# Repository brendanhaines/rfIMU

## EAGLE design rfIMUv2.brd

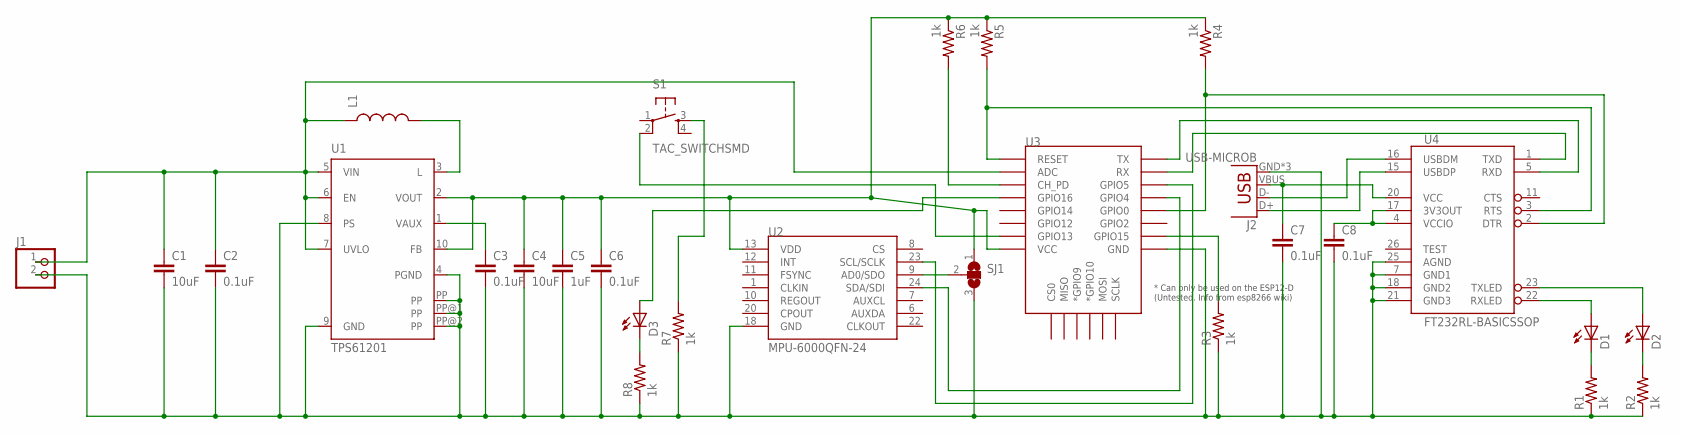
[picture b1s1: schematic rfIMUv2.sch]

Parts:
C1, C4: 10uF; C0603
C2, C3, C6, C7, C8: 0.1uF; C0603
C5: 1uF; C0603
D1, D2: LEDCHIPLED_0603; CHIPLED_0603
D3: LEDCHIP-LED0603; CHIP-LED0603
J1: PINHD-1X2; 1X02
J2: USB-MICROB
L1: INDUCTOR0805; 0805
R1, R2, R3, R4, R5, R6, R7, R8: 1k; R0603
S1: TAC_SWITCHSMD; TACTILE-SWITCH-SMD
SJ1: SJ2W; SJ_2
U1: TPS61201; S-PDSO-N10
U2: MPU-6000QFN-24; QFN-24-TESTING
U3: ESP12ESMD; ESP12E-SMD
U4: FT232RL-BASICSSOP; SSOP28DB

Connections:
3V3: C4.1, C5.1, C6.1, R4.1, R5.1, R6.1, SJ1.1, U1.2 (VOUT), U1.10 (FB), U2.13 (VDD), U3.VCC
D2: D2.C, R2.2
DRX: U3.RXD0 (RX), U4.1 (TXD)
DTR: R4.2, U3.GPIO0, U4.2 (DTR)
DTX: U3.TXD0 (TX), U4.5 (RXD)
GND: C1.2, C2.2, C3.2, C4.2, C5.2, C6.2, C7.2, C8.2, J1.2, J2.GND, J2.MT1 (GND), J2.MT2 (GND), R1.1, R2.1, R3.1, R7.1, R8.1, SJ1.3, U1.4 (PGND), U1.8 (PS), U1.9 (GND), U1.PP, U1.PP@1 (PP), U1.PP@2 (PP), U2.18 (GND), U3.GND, U4.7 (GND1), U4.18 (GND2), U4.21 (GND3), U4.25 (AGND)
unnamed: R3.2, U3.GPIO15
unnamed: R6.2, U3.CH_PD
unnamed: D2.A, U4.23 (TXLED)
unnamed: D1.A, U4.22 (RXLED)
unnamed: D1.C, R1.2
unnamed: C3.1, U1.1 (VAUX)
unnamed: SJ1.2, U2.9 (AD0/SDO)
unnamed: C8.1, U4.4 (VCCIO), U4.17 (3V3OUT)
unnamed: L1.2, U1.3 (L)
unnamed: S1.2, U3.GPIO13
unnamed: R7.2, S1.3
unnamed: D3.A, U3.GPIO16
unnamed: D3.C, R8.2
RESET: R5.2, U3.RESET, U4.3 (RTS)
SCL: U2.23 (SCL/SCLK), U3.GPIO5
SDA: U2.24 (SDA/SDI), U3.GPIO4
USBD+: J2.D+, U4.15 (USBDP)
USBD-: J2.D-, U4.16 (USBDM)
VIN: C1.1, C2.1, J1.1, L1.1, U1.5 (VIN), U1.6 (EN), U1.7 (UVLO), U3.ADC
VUSB: C7.1, J2.VBUS, U4.20 (VCC)

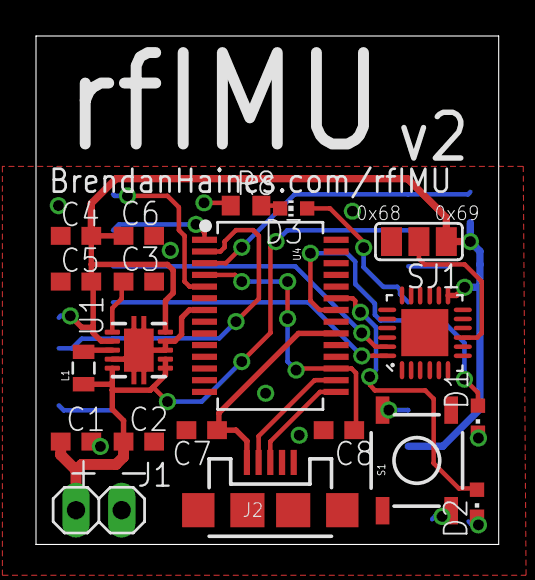
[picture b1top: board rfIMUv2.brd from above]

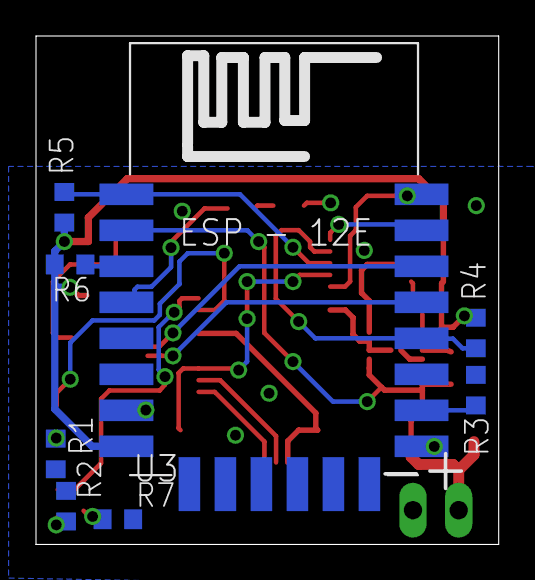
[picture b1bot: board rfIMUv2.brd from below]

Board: 2 copper layers, 25.7 x 28.2 mm, 28 parts (8 on the bottom side), 26 nets.

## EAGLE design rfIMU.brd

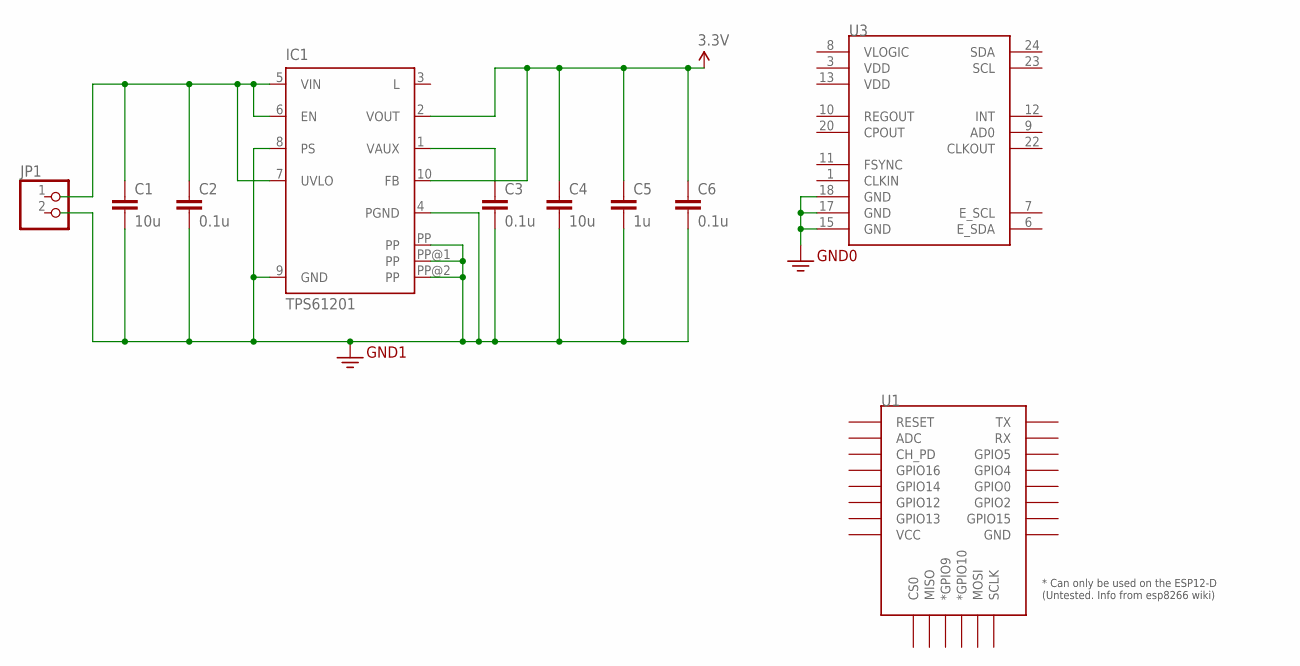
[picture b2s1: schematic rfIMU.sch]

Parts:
C1, C4: 10u; 0603
C2, C3, C6: 0.1u; 0603
C5: 1u; 0603
IC1: TPS61201; S-PDSO-N10
JP1: PINHD-1X2; 1X02
U1: ESP12ESMD; ESP12E-SMD
U3: MPU-9150QFN-24-NP; QFN-24-NP

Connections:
3.3V: C1.2, C2.2, C3.2, C4.1, C4.2, C5.1, C5.2, C6.1, C6.2, IC1.2 (VOUT), IC1.4 (PGND), IC1.8 (PS), IC1.9 (GND), IC1.10 (FB), IC1.PP, IC1.PP@1 (PP), IC1.PP@2 (PP), U3.15 (GND), U3.17 (GND), U3.18 (GND)
unnamed: C3.1, IC1.1 (VAUX)
unnamed: C1.1, C2.1, IC1.5 (VIN), IC1.6 (EN), IC1.7 (UVLO)

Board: 2 copper layers, 10 parts (1 on the bottom side), 3 nets, no tracks yet.

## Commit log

2016-07-02 init
2016-07-02 adds schematic/board
2016-07-02 updates DRC rules
2016-07-15 adds v2

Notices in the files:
parts and their libraries:
SparkFun-Sensors: Licensing: Creative Commons ShareAlike 4.0 International - https://creativecommons.org/licenses/by-sa/4.0
